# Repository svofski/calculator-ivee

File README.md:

# Design files for IVEE Forth-based calculator

The original is here: https://github.com/zooxo/iv ( [Youtube demo](https://www.youtube.com/watch?v=m1aFRhqvuLM) )

Expectation:

Reality:

[Youtube video of IVEE](https://www.youtube.com/watch?v=LmGt2pndoQI)

### KiCad project

[Open in kicanvas.org](https://kicanvas.org/?github=https%3A%2F%2Fgithub.com%2Fsvofski%2Fcalculator-ivee%2Ftree%2Fmaster%2Fhardware%2Fcalc)

### Parts reference:

OLED 2.42 inch https://aliexpress.com/item/32950307344.html

switches SKRRAAE010 https://aliexpress.com/item/1005004917288663.html

on/off switch MSK-12C02 https://aliexpress.com/item/4000685483225.html

### Other

Battery shared load circuits:

 * https://forum.arduino.cc/t/proper-usage-of-lithium-charger-based-on-tp4056/477206/2
 * https://forum.arduino.cc/t/powering-a-pro-micro-board-with-li-ion-battery-and-usb-connector/572981/3

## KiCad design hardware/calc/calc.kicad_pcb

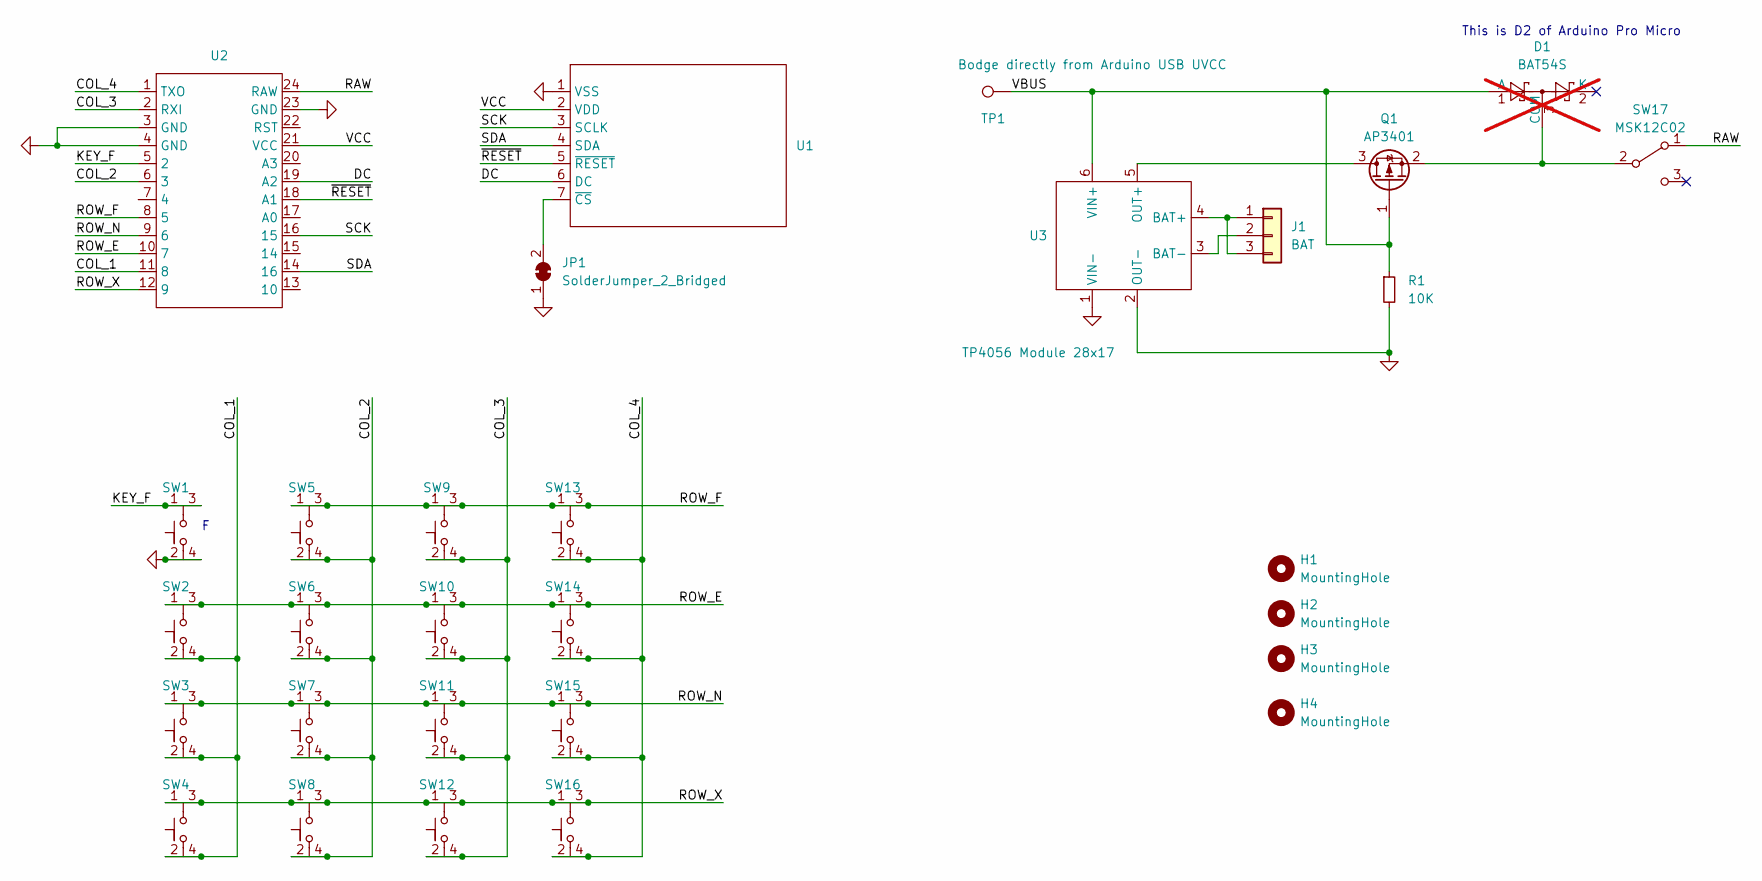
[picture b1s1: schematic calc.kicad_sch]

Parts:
D1: BAT54S; SOT-23; not fitted
H1, H2, H3, H4: MountingHole; MountingHole_3.2mm_M3
J1: BAT; PinHeader_1x03_P2.54mm_Vertical
JP1: SolderJumper_2_Bridged; SolderJumper-2_P1.3mm_Bridged_Pad1.0x1.5mm
Q1: AP3401; SOT-23
R1: 10K; R_0805_2012Metric
SW1, SW2, SW3, SW4, SW5, SW6, SW7, SW8, SW9, SW10, SW11, SW12, SW13, SW14, SW15, SW16: SKRRAAE010-15.24mm-keyboard-pitch
SW17: MSK12C02
TP1: Bodge directly from Arduino USB UVCC; TestPoint_THTPad_2.0x2.0mm_Drill1.0mm
U1: OLED_2.42inch_SPI_7PIN
U2: Arduino Pro Micro USB-C 36.8x17.7
U3: TP4056 Module 28x17

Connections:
/COL_1: SW2.2, SW2.4, SW3.2, SW3.4, SW4.2, SW4.4, U2.11 (8)
/COL_2: SW5.2, SW5.4, SW6.2, SW6.4, SW7.2, SW7.4, SW8.2, SW8.4, U2.6 (3)
/COL_3: SW9.2, SW9.4, SW10.2, SW10.4, SW11.2, SW11.4, SW12.2, SW12.4, U2.2 (RXI)
/COL_4: SW13.2, SW13.4, SW14.2, SW14.4, SW15.2, SW15.4, SW16.2, SW16.4, U2.1 (TXO)
/DC: U1.6 (DC), U2.19 (A2)
/KEY_F: SW1.1, SW1.3, U2.5 (2)
/RAW: SW17.1 (A), U2.24 (RAW)
/ROW_E: SW2.1, SW2.3, SW6.1, SW6.3, SW10.1, SW10.3, SW14.1, SW14.3, U2.10 (7)
/ROW_F: SW5.1, SW5.3, SW9.1, SW9.3, SW13.1, SW13.3, U2.8 (5)
/ROW_N: SW3.1, SW3.3, SW7.1, SW7.3, SW11.1, SW11.3, SW15.1, SW15.3, U2.9 (6)
/ROW_X: SW4.1, SW4.3, SW8.1, SW8.3, SW12.1, SW12.3, SW16.1, SW16.3, U2.12 (9)
/SCK: U1.3 (SCLK), U2.16 (15)
/SDA: U1.4 (SDA), U2.14 (16)
/VBUS: D1.1 (A), Q1.1 (G), R1.1, TP1.1, U3.6 (VIN+)
/VCC: U1.2 (VDD), U2.21 (VCC)
/~RESET: U1.5 (~RESET), U2.18 (A1)
GND: JP1.1 (A), R1.2, SW1.2, SW1.4, U1.1 (VSS), U2.3 (GND), U2.4 (GND), U2.23 (GND), U3.1 (VIN-), U3.2 (OUT-)
unnamed: D1.3 (COM), Q1.2 (S), SW17.2 (B)
unnamed: J1.1, J1.3, U3.4 (BAT+)
unnamed: J1.2, U3.3 (BAT-)
unnamed: JP1.2 (B), U1.7 (~CS)
unnamed: Q1.3 (D), U3.5 (OUT+)

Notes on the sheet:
This is D2 of Arduino Pro Micro

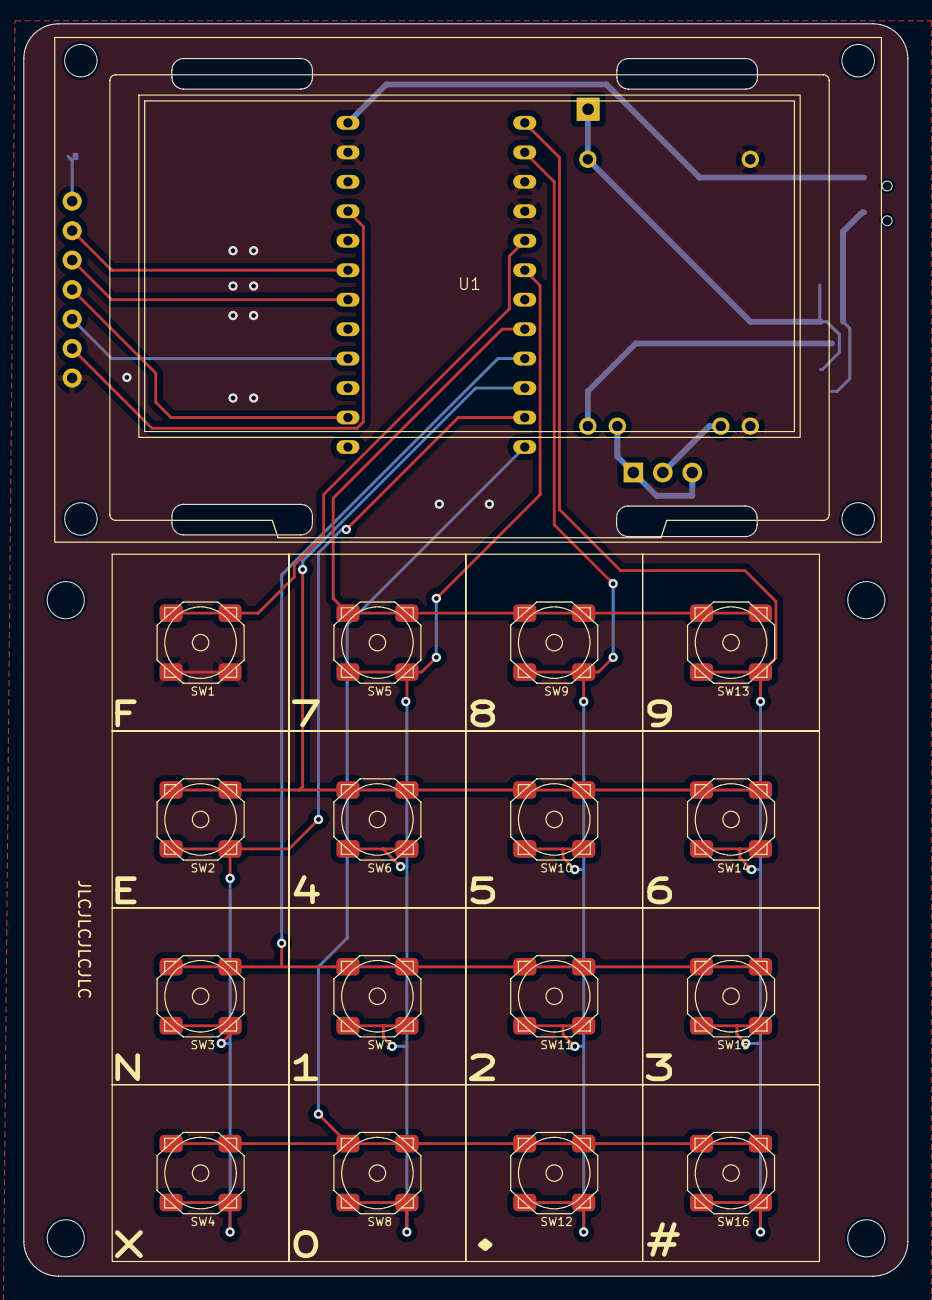
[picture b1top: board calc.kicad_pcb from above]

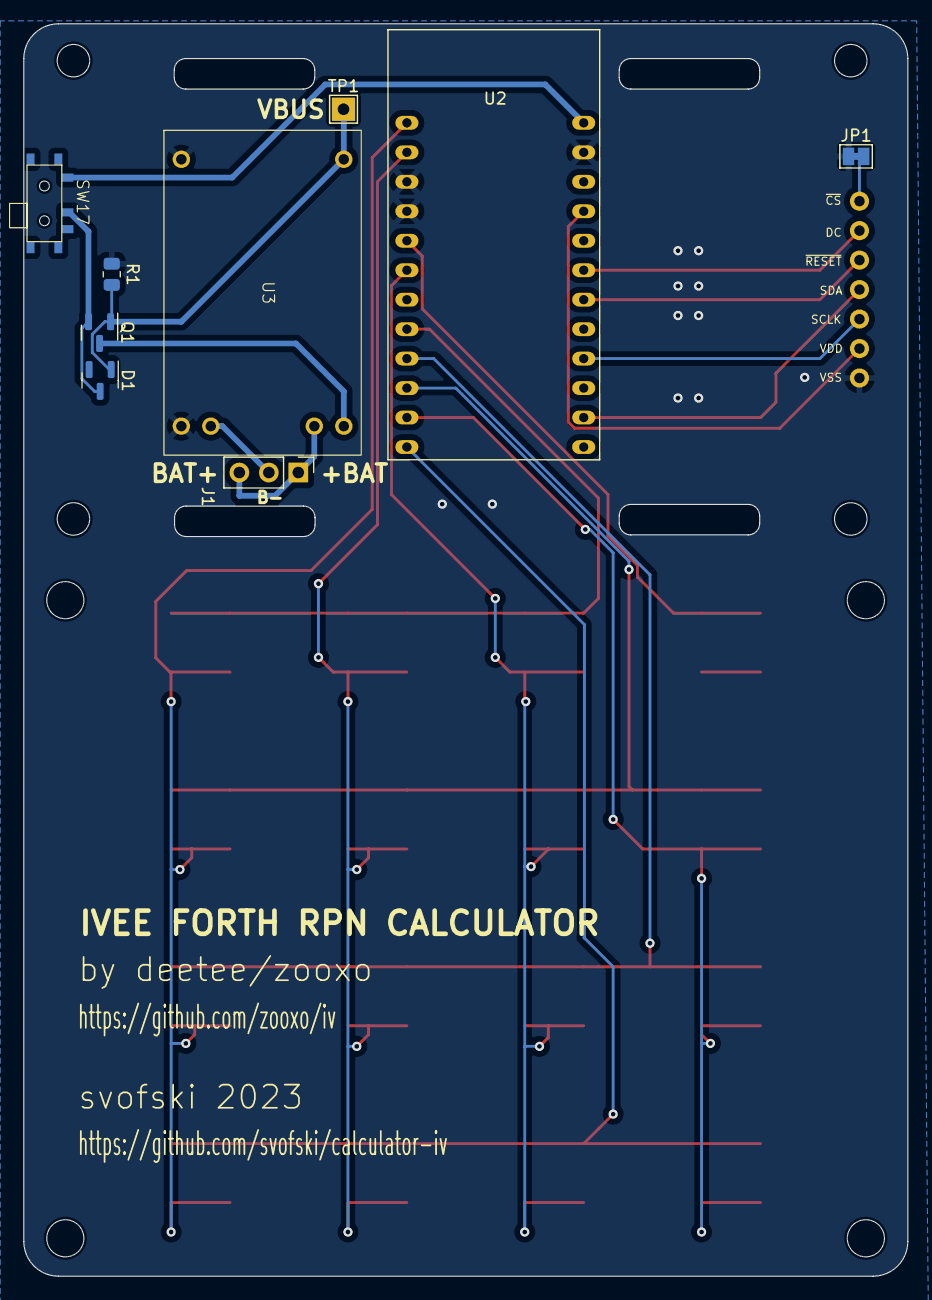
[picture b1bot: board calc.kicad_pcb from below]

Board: 2 copper layers, 76.2 x 107.9 mm, 30 parts (9 on the bottom side), 22 nets.

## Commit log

2023-09-12 gitignore
2023-09-12 graphics
2024-01-27 updated kicad files
2026-04-19 3dprintering files
